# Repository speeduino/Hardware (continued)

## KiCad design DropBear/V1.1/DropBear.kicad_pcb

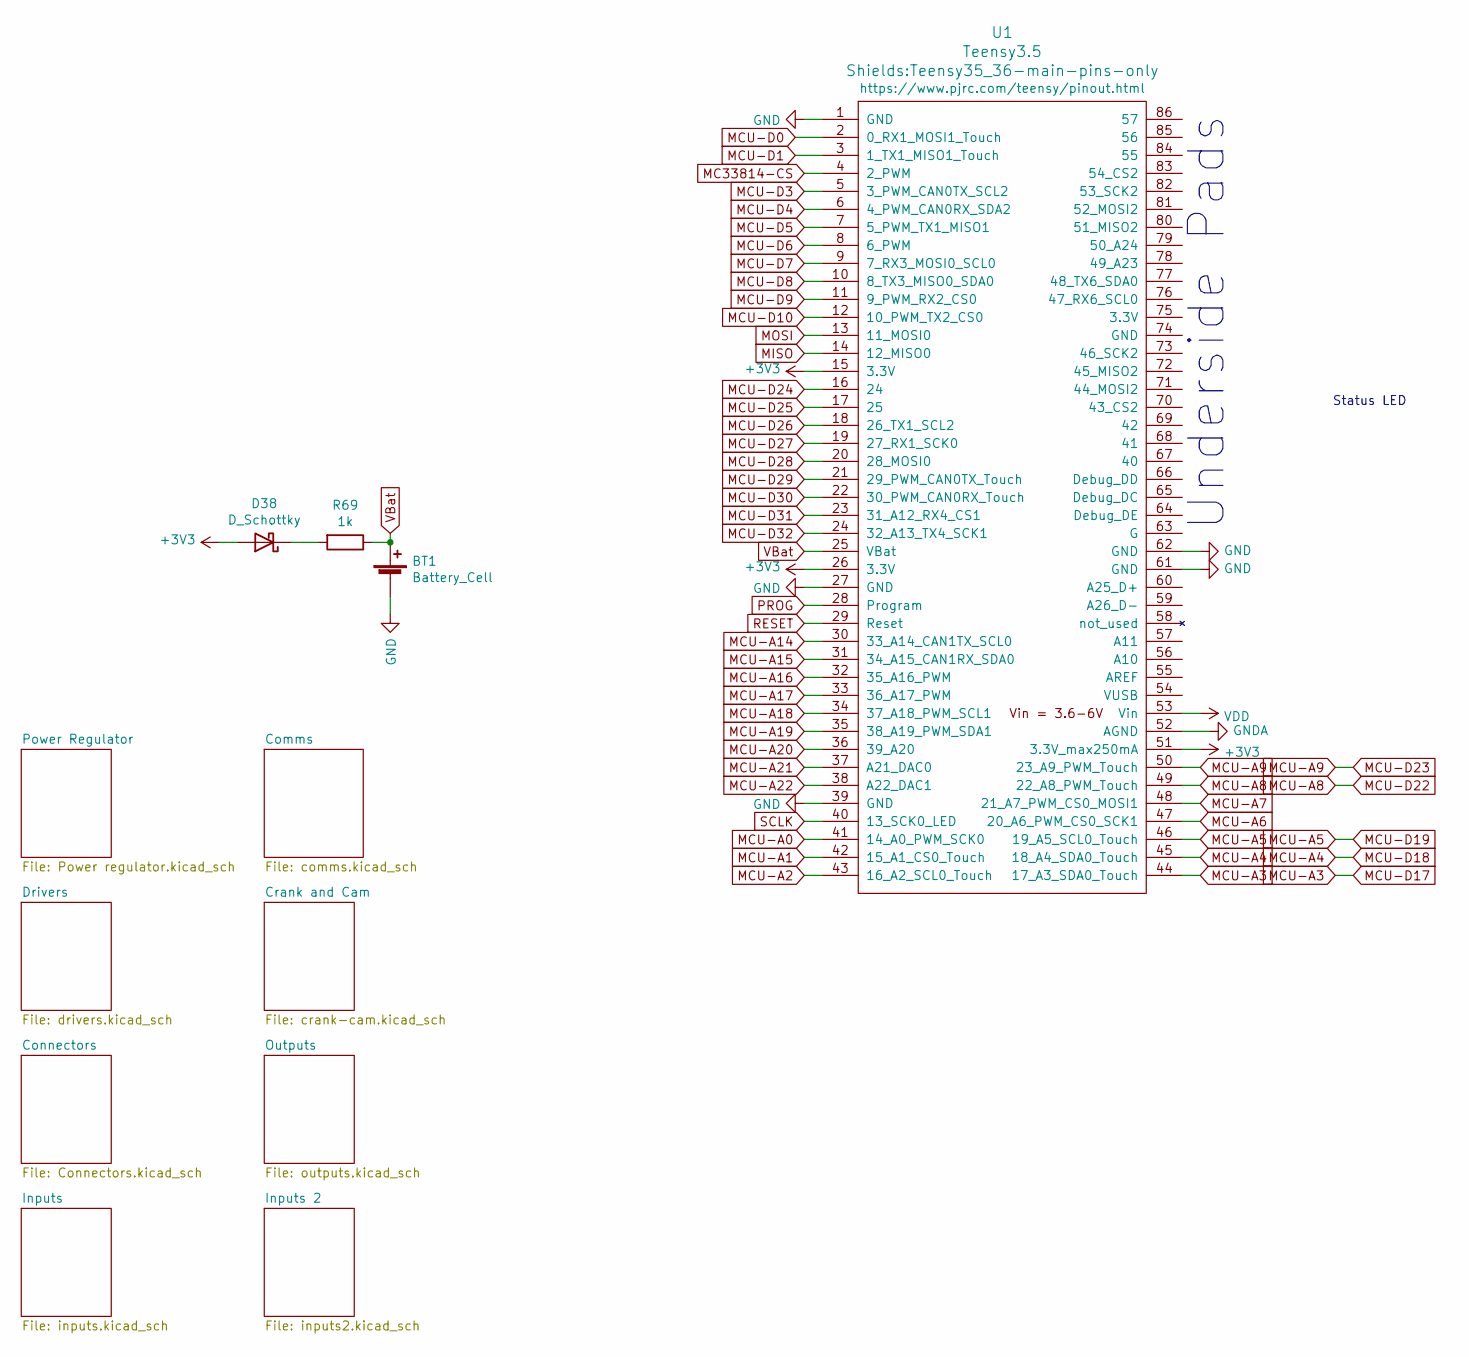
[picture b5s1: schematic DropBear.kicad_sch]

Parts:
BT1: Battery_Cell; 2999; Manufacturer_Part_Number 2999; Digikey Part Number 36-2999-ND
D38: D_Schottky; D_PowerDI-123; Manufacturer_Part_Number DFLS2100-7; Digikey Part Number DFLS2100-7DICT-ND
R69: 1k; R_0805_2012Metric; Manufacturer_Part_Number RC0805FR-071KL; Digikey Part Number 311-1.00KCRCT-ND
U1: Teensy3.5; Teensy35_36-main-pins-only

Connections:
+3V3: D38.2 (A), U1.15 (3.3V), U1.26 (3.3V), U1.51 (3.3V_max250mA); also elsewhere on the board
+5V: U1.53 (Vin); also elsewhere on the board
ADC-Clamp-3: U1.34 (37_A18_PWM_SCL1); also elsewhere on the board
ADC-Clamp-4: U1.33 (36_A17_PWM); also elsewhere on the board
ADC-Clamp-5: U1.32 (35_A16_PWM); also elsewhere on the board
ADC-Clamp-6: U1.31 (34_A15_CAN1RX_SDA0); also elsewhere on the board
ADC-Clamp-7: U1.30 (33_A14_CAN1TX_SCL0); also elsewhere on the board
ADC-Clamp-11: U1.35 (38_A19_PWM_SDA1); also elsewhere on the board
ADC-Clamp-12: U1.36 (39_A20); also elsewhere on the board
ADC-Clamp-13: U1.37 (A21_DAC0); also elsewhere on the board
ADC-Clamp-14: U1.38 (A22_DAC1); also elsewhere on the board
GND: BT1.2 (-), U1.1 (GND), U1.27 (GND), U1.39 (GND), U1.61 (GND), U1.62 (GND); also elsewhere on the board
GNDA: U1.52 (AGND); also elsewhere on the board
MC33810_1-CS: U1.12 (10_PWM_TX2_CS0); also elsewhere on the board
MC33810_2-CS: U1.11 (9_PWM_RX2_CS0); also elsewhere on the board
MC33814-CS: U1.4 (2_PWM); also elsewhere on the board
MCU-A0: U1.41 (14_A0_PWM_SCK0); also elsewhere on the board
MCU-A1: U1.42 (15_A1_CS0_Touch); also elsewhere on the board
MCU-A2: U1.43 (16_A2_SCL0_Touch)
MCU-A3: U1.44 (17_A3_SDA0_Touch)
MCU-A4: U1.45 (18_A4_SDA0_Touch); also elsewhere on the board
MCU-A5: U1.46 (19_A5_SCL0_Touch); also elsewhere on the board
MCU-A6: U1.47 (20_A6_PWM_CS0_SCK1)
MCU-A7: U1.48 (21_A7_PWM_CS0_MOSI1)
MCU-A8: U1.49 (22_A8_PWM_Touch); also elsewhere on the board
MCU-A9: U1.50 (23_A9_PWM_Touch); also elsewhere on the board
MCU-D0: U1.2 (0_RX1_MOSI1_Touch); also elsewhere on the board
MCU-D1: U1.3 (1_TX1_MISO1_Touch); also elsewhere on the board
MCU-D3: U1.5 (3_PWM_CAN0TX_SCL2); also elsewhere on the board
MCU-D4: U1.6 (4_PWM_CAN0RX_SDA2); also elsewhere on the board
MCU-D5: U1.7 (5_PWM_TX1_MISO1); also elsewhere on the board
MCU-D6: U1.8 (6_PWM); also elsewhere on the board
MCU-D7: U1.9 (7_RX3_MOSI0_SCL0); also elsewhere on the board
MCU-D8: U1.10 (8_TX3_MISO0_SDA0); also elsewhere on the board
MCU-D24: U1.16 (24); also elsewhere on the board
MCU-D25: U1.17 (25); also elsewhere on the board
MCU-D26: U1.18 (26_TX1_SCL2); also elsewhere on the board
MCU-D27: U1.19 (27_RX1_SCK0); also elsewhere on the board
MCU-D28: U1.20 (28_MOSI0); also elsewhere on the board
MCU-D29: U1.21 (29_PWM_CAN0TX_Touch); also elsewhere on the board
MCU-D30: U1.22 (30_PWM_CAN0RX_Touch); also elsewhere on the board
MCU-D31: U1.23 (31_A12_RX4_CS1); also elsewhere on the board
MCU-D32: U1.24 (32_A13_TX4_SCK1); also elsewhere on the board
MISO: U1.14 (12_MISO0); also elsewhere on the board
MOSI: U1.13 (11_MOSI0); also elsewhere on the board
unnamed: D38.1 (K), R69.2
PROG: U1.28 (Program)
RESET: U1.29 (Reset)
SCLK: U1.40 (13_SCK0_LED); also elsewhere on the board
VBat: BT1.1 (+), R69.1, U1.25 (VBat)

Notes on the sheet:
Underside Pads
Status LED

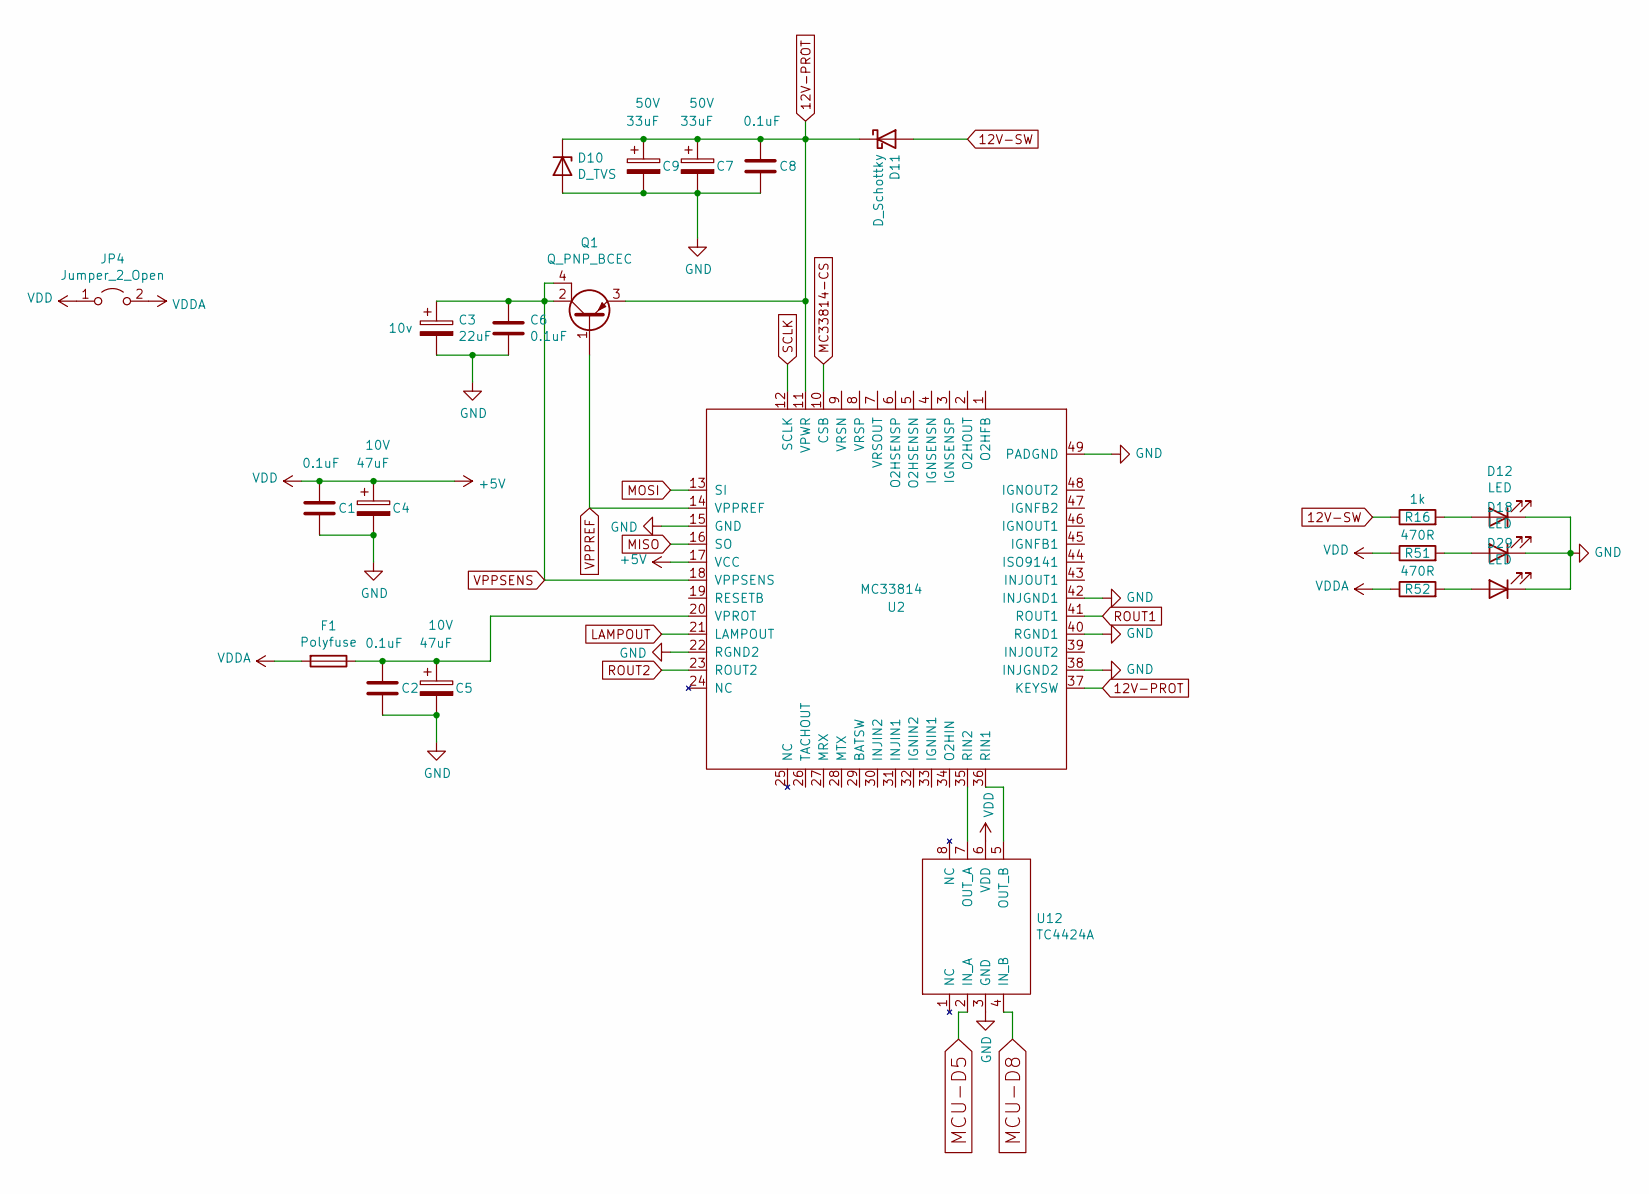
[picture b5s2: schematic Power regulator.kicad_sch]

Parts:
C1, C2, C6, C8: 0.1uF; C_0805_2012Metric; Manufacturer_Part_Number CC0805KRX7R9BB104; Digikey Part Number 311-1140-1-ND
C3: 22uF; CP_Elec_4x5.4; Voltage 10v; Manufacturer_Part_Number PCE3882CT-ND; Digikey Part Number EEE-1CA220WR
C4, C5: 47uF; CP_EIA-3528-21_Kemet-B; Voltage 10V; Manufacturer_Part_Number TAJB476K006RNJ; Digikey Part Number 478-1692-1-ND
C7, C9: 33uF; CP_Elec_6.3x7.7; Voltage 50V; Manufacturer_Part_Number EEE-1HA330XP; Digikey Part Number PCE3925CT-ND
D10: D_TVS; D_SMB; Manufacturer_Part_Number SMBJ40A-Q; Digikey Part Number SMBJ40A-QCT-ND
D11: D_Schottky; D_SMA_Handsoldering; Manufacturer_Part_Number B360A-13-F; Digikey Part Number B360A-FDICT-ND
D12, D18, D29: LED; LED_0805_2012Metric_Pad1.15x1.40mm_HandSolder; Manufacturer_Part_Number LG R971-KN-1; Digikey Part Number 475-1410-2-ND
F1: Polyfuse; Fuse_0603_1608Metric; Manufacturer_Part_Number 0ZCM0008FF2G; Digikey Part Number 507-1817-1-ND
JP4: Jumper_2_Open; SolderJumper-2_P1.3mm_Open_Pad1.0x1.5mm
Q1: Q_PNP_BCEC; SOT-223-3_TabPin2; Manufacturer_Part_Number FZT753TA; Digikey Part Number FZT753CT-ND
R16: 1k; R_0805_2012Metric; Manufacturer_Part_Number RC0805FR-071KL; Digikey Part Number 311-1.00KCRCT-ND
R51, R52: 470R; R_0805_2012Metric; Manufacturer_Part_Number ERJ-6ENF4700V; Digikey Part Number P470CCT-ND
U2: MC33814; LQFP-48-1EP_7x7mm_P0.5mm_EP3.6x3.6mm_ThermalVias; Manufacturer_Part_Number MC33814AE
U12: TC4424A; SOIC-8_3.9x4.9mm_P1.27mm; Manufacturer_Part_Number TC4424AVOA; Digikey Part Number TC4424AVOA-ND

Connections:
12V-PROT: C7.1, C8.1, C9.1, D10.1 (K), D11.1 (K), Q1.3 (E), U2.11 (VPWR), U2.37 (KEYSW)
12V-SW: D11.2 (A), R16.1; also elsewhere on the board
+5V: C1.1, C4.1, JP4.1 (A), R51.1, U2.17 (VCC), U12.6 (VDD); also elsewhere on the board
GND: C1.2, C2.2, C3.2, C4.2, C5.2, C6.2, C7.2, C8.2, C9.2, D10.2 (A), D12.1 (K), D18.1 (K), D29.1 (K), U2.15 (GND), U2.22 (RGND2), U2.38 (INJGND2), U2.40 (RGND1), U2.42 (INJGND1), U2.49 (PADGND), U12.3 (GND); also elsewhere on the board
LAMPOUT: U2.21 (LAMPOUT)
MC33814-CS: U2.10 (CSB); also elsewhere on the board
MCU-D5: U12.2 (IN_A); also elsewhere on the board
MCU-D8: U12.4 (IN_B); also elsewhere on the board
MISO: U2.16 (SO); also elsewhere on the board
MOSI: U2.13 (SI); also elsewhere on the board
unnamed: C2.1, C5.1, F1.1, U2.20 (VPROT)
unnamed: D12.2 (A), R16.2
unnamed: D18.2 (A), R51.2
unnamed: D29.2 (A), R52.2
unnamed: U2.36 (RIN1), U12.5 (OUT_B)
unnamed: U2.35 (RIN2), U12.7 (OUT_A)
ROUT2: U2.23 (ROUT2); also elsewhere on the board
SCLK: U2.12 (SCLK); also elsewhere on the board
VDDA: F1.2, JP4.2 (B), R52.1; also elsewhere on the board
VPPREF: Q1.1 (B), U2.14 (VPPREF)
VPPSENS: C3.1, C6.1, Q1.2 (C), Q1.4 (C), U2.18 (VPPSENS)

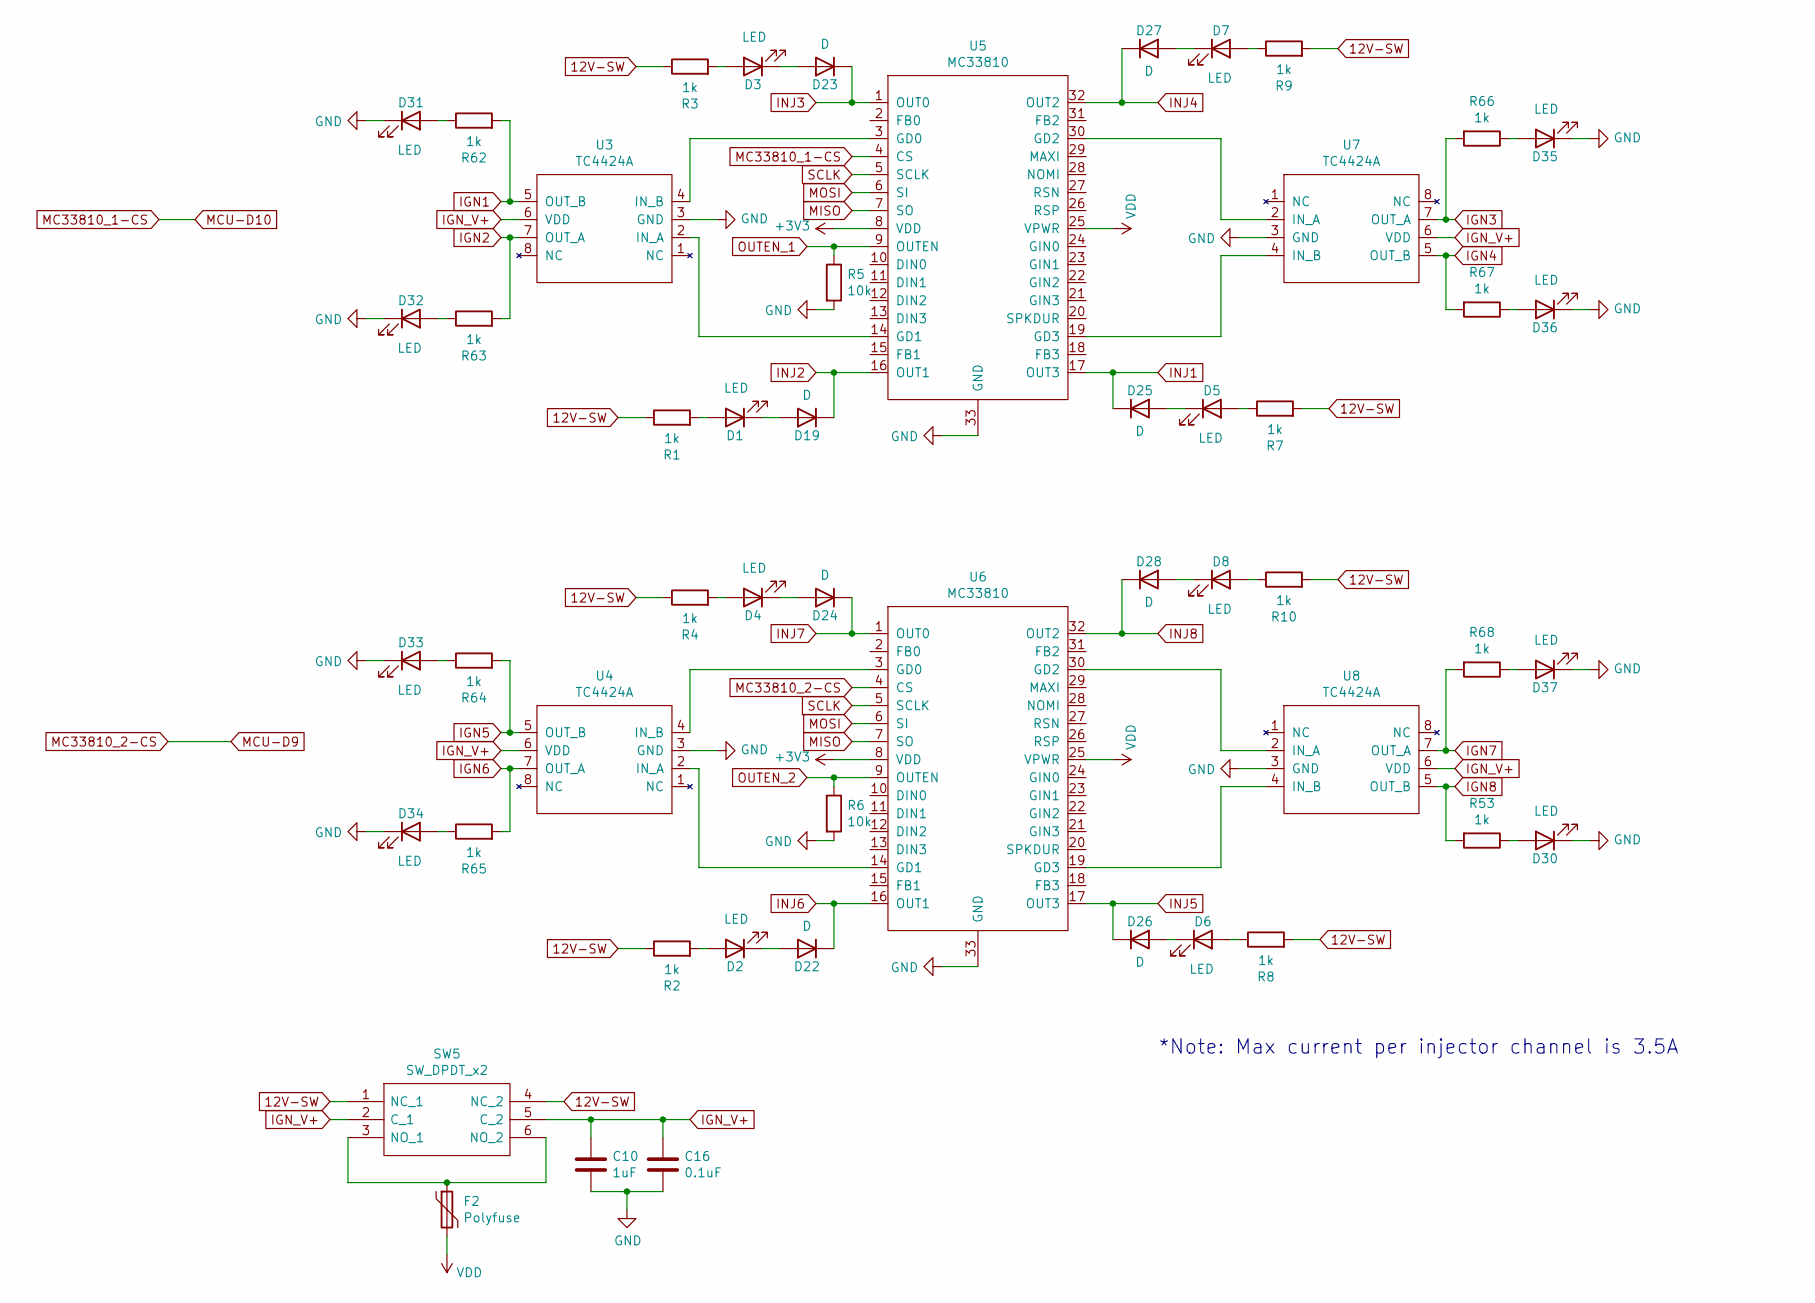
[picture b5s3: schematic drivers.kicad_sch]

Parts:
C10: 1uF; C_0805_2012Metric; Manufacturer_Part_Number CC0805KKX7R7BB105; Digikey Part Number 311-1365-1-ND
C16: 0.1uF; C_0805_2012Metric; Manufacturer_Part_Number CC0805KRX7R9BB104; Digikey Part Number 311-1140-1-ND
D1, D2, D3, D4, D5, D6, D7, D8: LED; LED_0805_2012Metric; Manufacturer_Part_Number LH R974-LP-1; Digikey Part Number 475-1415-1-ND
D19, D22, D23, D24, D25, D26, D27, D28: D; D_SOD-323; Manufacturer_Part_Number 1N4448WX-TP; Digikey Part Number 1N4448WXTPMSCT-ND
D30, D31, D32, D33, D34, D35, D36, D37: LED; LED_0805_2012Metric; Manufacturer_Part_Number SML-H12D8TT86C; Digikey Part Number SML-H12D8TT86CCT-ND
F2: Polyfuse; Fuse_1812_4532Metric; Manufacturer_Part_Number 0ZCC0050FF2C; Digikey Part Number 507-1361-1-ND
R1, R2, R3, R4, R7, R8, R9, R10, R53, R62, R63, R64, R65, R66, R67, R68: 1k; R_0805_2012Metric; Manufacturer_Part_Number RC0805FR-071KL; Digikey Part Number 311-1.00KCRCT-ND
R5, R6: 10k; R_0805_2012Metric; Manufacturer_Part_Number RC0805JR-0710KL; Digikey Part Number 311-10KARCT-ND
SW5: SW_DPDT_x2; AYZ0202AGRLC; Manufacturer_Part_Number AYZ0202AGRLC; Digikey Part Number 401-2013-1-ND
U3, U4, U7, U8: TC4424A; SOIC-8_3.9x4.9mm_P1.27mm; Manufacturer_Part_Number TC4424AVOA; Digikey Part Number TC4424AVOA-ND
U5, U6: MC33810; SOIC32-P0.65-33N; Manufacturer_Part_Number MCZ33810EK

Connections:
12V-SW: R1.1, R2.1, R3.1, R4.1, R7.2, R8.2, R9.2, R10.2, SW5.1 (NC_1), SW5.4 (NC_2); also elsewhere on the board
+3V3: U5.8 (VDD), U6.8 (VDD); also elsewhere on the board
+5V: F2.2, U5.25 (VPWR), U6.25 (VPWR); also elsewhere on the board
GND: C10.2, C16.2, D30.1 (K), D31.1 (K), D32.1 (K), D33.1 (K), D34.1 (K), D35.1 (K), D36.1 (K), D37.1 (K), R5.2, R6.2, U3.3 (GND), U4.3 (GND), U5.33 (GND), U6.33 (GND), U7.3 (GND), U8.3 (GND); also elsewhere on the board
IGN1: R62.2, U3.5 (OUT_B); also elsewhere on the board
IGN2: R63.2, U3.7 (OUT_A); also elsewhere on the board
IGN3: R66.2, U7.7 (OUT_A); also elsewhere on the board
IGN4: R67.2, U7.5 (OUT_B); also elsewhere on the board
IGN5: R64.2, U4.5 (OUT_B); also elsewhere on the board
IGN6: R65.2, U4.7 (OUT_A); also elsewhere on the board
IGN7: R68.2, U8.7 (OUT_A); also elsewhere on the board
IGN8: R53.2, U8.5 (OUT_B); also elsewhere on the board
IGN_V+: C10.1, C16.1, SW5.2 (C_1), SW5.5 (C_2), U3.6 (VDD), U4.6 (VDD), U7.6 (VDD), U8.6 (VDD)
INJ1: D25.1 (K), U5.17 (OUT3); also elsewhere on the board
INJ2: D19.1 (K), U5.16 (OUT1); also elsewhere on the board
INJ3: D23.1 (K), U5.1 (OUT0); also elsewhere on the board
INJ4: D27.1 (K), U5.32 (OUT2); also elsewhere on the board
INJ5: D26.1 (K), U6.17 (OUT3); also elsewhere on the board
INJ6: D22.1 (K), U6.16 (OUT1); also elsewhere on the board
INJ7: D24.1 (K), U6.1 (OUT0); also elsewhere on the board
INJ8: D28.1 (K), U6.32 (OUT2); also elsewhere on the board
MC33810_1-CS: U5.4 (CS); also elsewhere on the board
MC33810_2-CS: U6.4 (CS); also elsewhere on the board
MISO: U5.7 (SO), U6.7 (SO); also elsewhere on the board
MOSI: U5.6 (SI), U6.6 (SI); also elsewhere on the board
unnamed: D1.1 (K), D19.2 (A)
unnamed: D1.2 (A), R1.2
unnamed: D2.1 (K), D22.2 (A)
unnamed: D2.2 (A), R2.2
unnamed: D3.2 (A), R3.2
unnamed: D4.2 (A), R4.2
unnamed: D5.2 (A), R7.1
unnamed: D6.2 (A), R8.1
unnamed: D7.2 (A), R9.1
unnamed: D8.2 (A), R10.1
unnamed: D3.1 (K), D23.2 (A)
unnamed: D4.1 (K), D24.2 (A)
unnamed: D5.1 (K), D25.2 (A)
unnamed: D6.1 (K), D26.2 (A)
unnamed: D7.1 (K), D27.2 (A)
unnamed: D8.1 (K), D28.2 (A)
unnamed: D30.2 (A), R53.1
unnamed: D31.2 (A), R62.1
unnamed: D32.2 (A), R63.1
unnamed: D33.2 (A), R64.1
unnamed: D34.2 (A), R65.1
unnamed: D35.2 (A), R66.1
unnamed: D36.2 (A), R67.1
unnamed: D37.2 (A), R68.1
unnamed: F2.1, SW5.3 (NO_1), SW5.6 (NO_2)
unnamed: U3.2 (IN_A), U5.14 (GD1)
unnamed: U3.4 (IN_B), U5.3 (GD0)
unnamed: U4.2 (IN_A), U6.14 (GD1)
unnamed: U4.4 (IN_B), U6.3 (GD0)
unnamed: U5.19 (GD3), U7.4 (IN_B)
unnamed: U5.30 (GD2), U7.2 (IN_A)
unnamed: U6.19 (GD3), U8.4 (IN_B)
unnamed: U6.30 (GD2), U8.2 (IN_A)
OUTEN_1: R5.1, U5.9 (OUTEN)
OUTEN_2: R6.1, U6.9 (OUTEN)
SCLK: U5.5 (SCLK), U6.5 (SCLK); also elsewhere on the board

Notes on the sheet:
*Note: Max current per injector channel is 3.5A

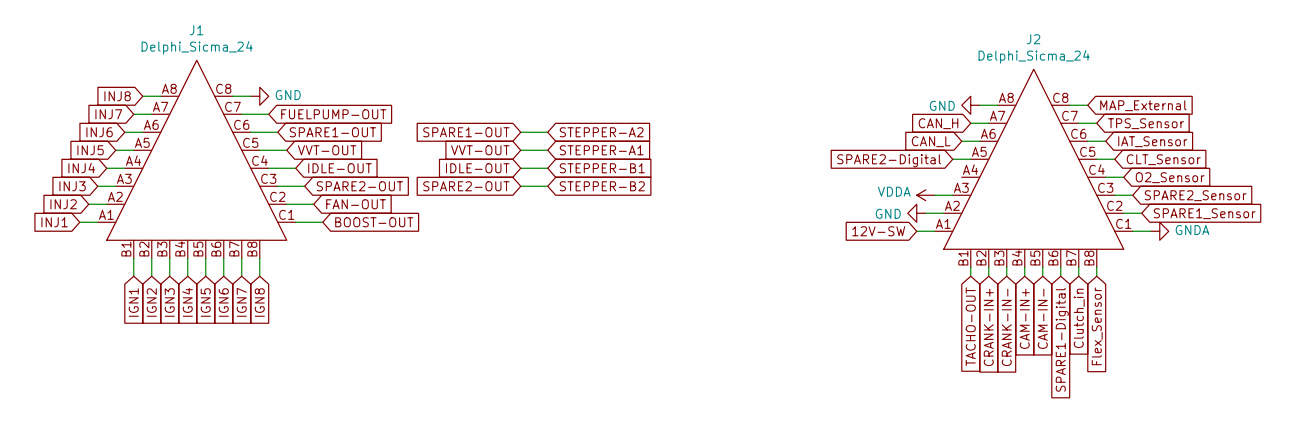
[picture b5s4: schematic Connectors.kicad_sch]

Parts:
J1: Delphi_Sicma_24; Delphi_Sicma_24_Grey
J2: Delphi_Sicma_24; Delphi_Sicma_24_Black

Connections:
12V-SW: J2.A1; also elsewhere on the board
ADC-Clamp-5: J2.B8; also elsewhere on the board
ADC-Clamp-6: J2.B7; also elsewhere on the board
BOOST-OUT: J1.C1; also elsewhere on the board
CAM-IN+: J2.B4; also elsewhere on the board
CAM-IN-: J2.B5; also elsewhere on the board
CAN_H: J2.A7; also elsewhere on the board
CAN_L: J2.A6; also elsewhere on the board
CLT_Sensor: J2.C5; also elsewhere on the board
CRANK-IN+: J2.B2; also elsewhere on the board
CRANK-IN-: J2.B3; also elsewhere on the board
FAN-OUT: J1.C2; also elsewhere on the board
GND: J1.C8, J2.A2, J2.A8; also elsewhere on the board
GNDA: J2.C1; also elsewhere on the board
IAT_Sensor: J2.C6; also elsewhere on the board
IDLE-OUT: J1.C4; also elsewhere on the board
IGN1: J1.B1; also elsewhere on the board
IGN2: J1.B2; also elsewhere on the board
IGN3: J1.B3; also elsewhere on the board
IGN4: J1.B4; also elsewhere on the board
IGN5: J1.B5; also elsewhere on the board
IGN6: J1.B6; also elsewhere on the board
IGN7: J1.B7; also elsewhere on the board
IGN8: J1.B8; also elsewhere on the board
INJ1: J1.A1; also elsewhere on the board
INJ2: J1.A2; also elsewhere on the board
INJ3: J1.A3; also elsewhere on the board
INJ4: J1.A4; also elsewhere on the board
INJ5: J1.A5; also elsewhere on the board
INJ6: J1.A6; also elsewhere on the board
INJ7: J1.A7; also elsewhere on the board
INJ8: J1.A8; also elsewhere on the board
MAP_External: J2.C8; also elsewhere on the board
O2_Sensor: J2.C4; also elsewhere on the board
ROUT2: J2.B1; also elsewhere on the board
SPARE1-Digital: J2.B6; also elsewhere on the board
SPARE1-OUT: J1.C6; also elsewhere on the board
SPARE1_Sensor: J2.C2; also elsewhere on the board
SPARE2-Digital: J2.A5; also elsewhere on the board
SPARE2-OUT: J1.C3; also elsewhere on the board
SPARE2_Sensor: J2.C3; also elsewhere on the board
STEPPER-A1: J1.C5; also elsewhere on the board
TPS_Sensor: J2.C7; also elsewhere on the board
VDDA: J2.A3; also elsewhere on the board

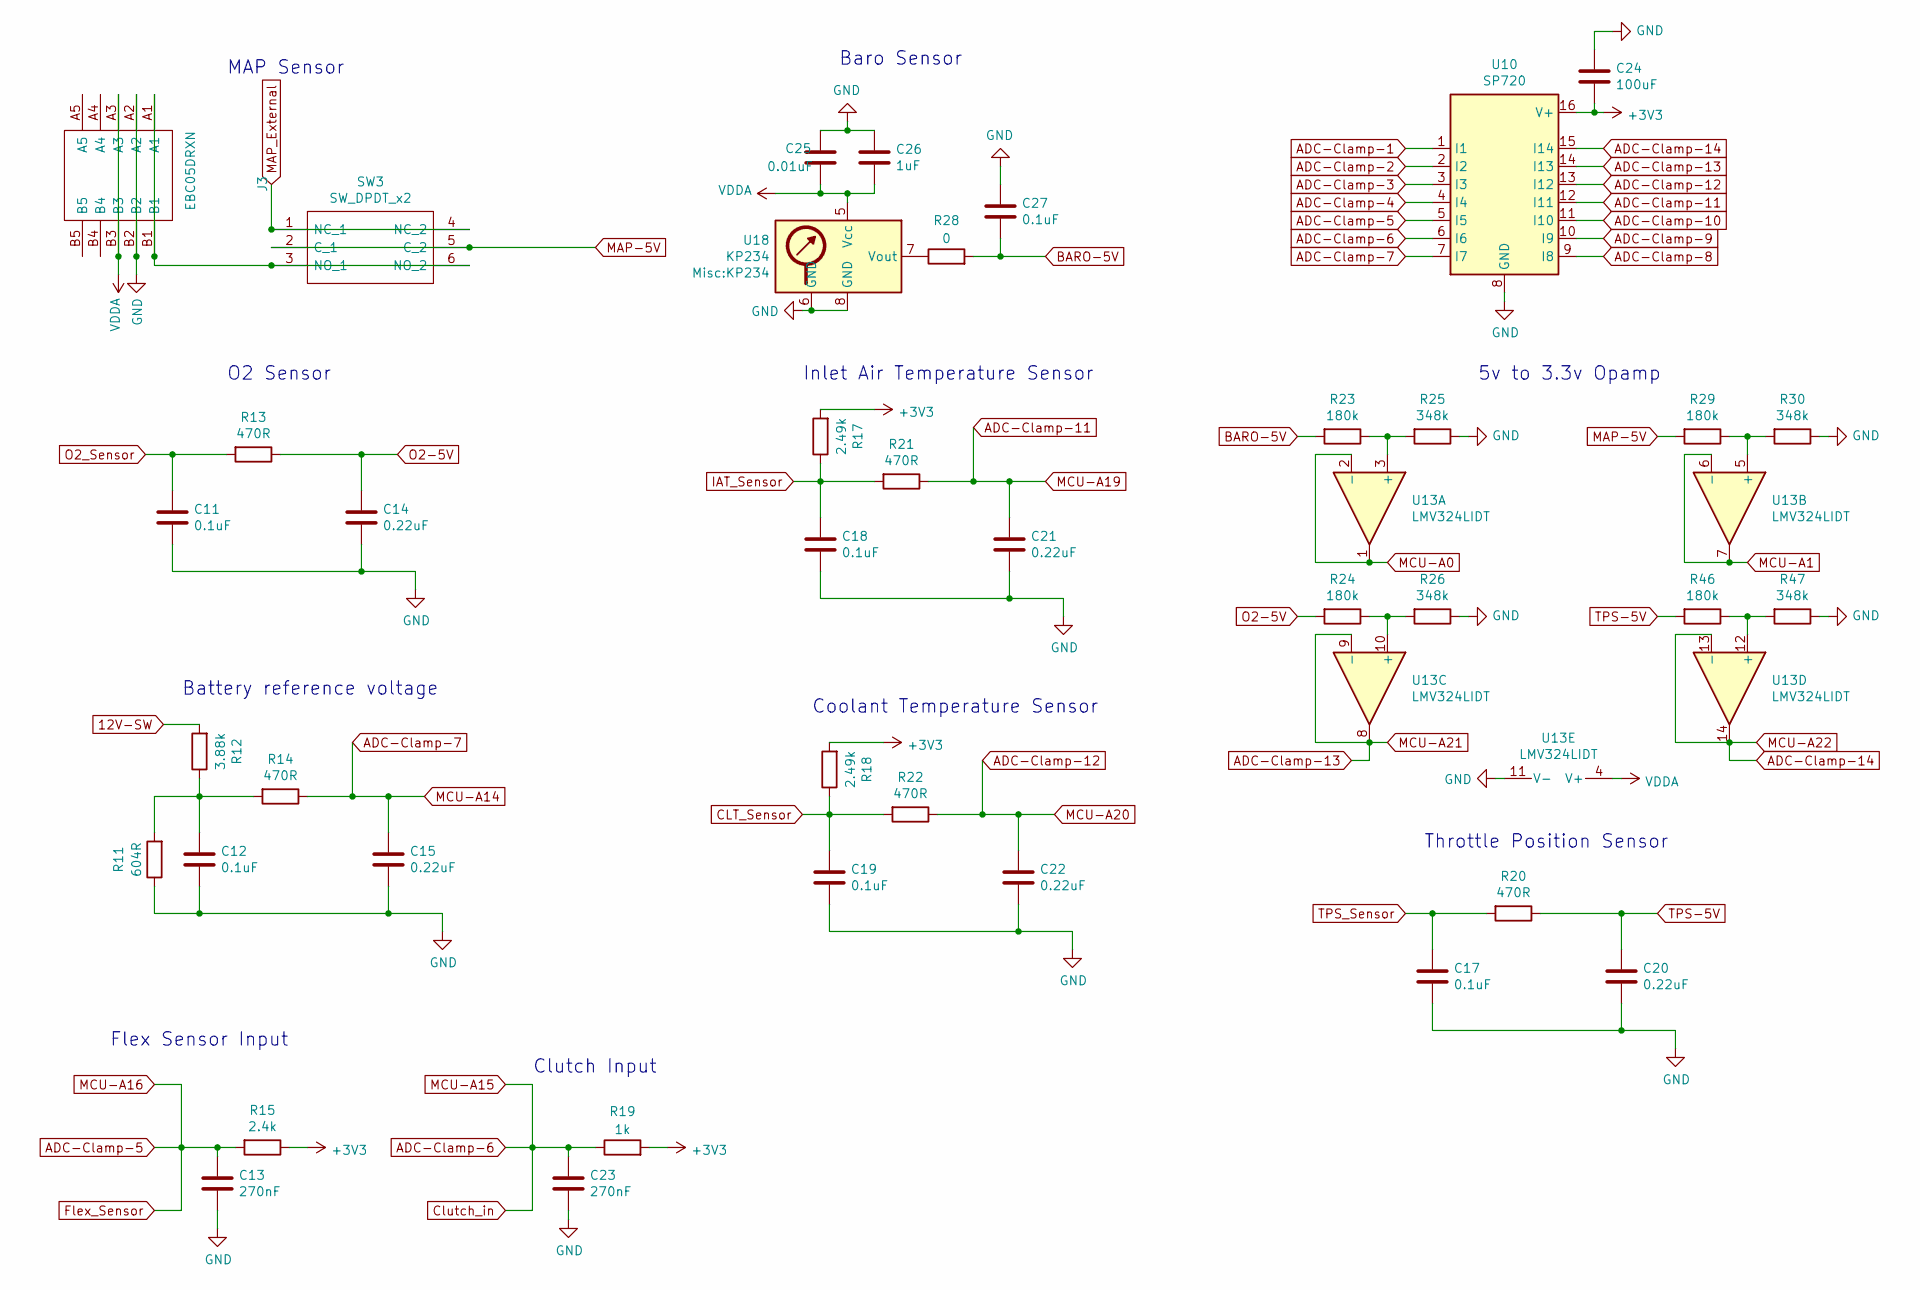
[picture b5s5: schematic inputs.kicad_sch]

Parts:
C11, C12, C17, C18, C19, C27: 0.1uF; C_0805_2012Metric; Manufacturer_Part_Number CC0805KRX7R9BB104; Digikey Part Number 311-1140-1-ND
C13, C23: 270nF; C_0805_2012Metric; Manufacturer_Part_Number CC0805JRX7R7BB274; Digikey Part Number 311-4268-1-ND
C14, C15, C20, C21, C22: 0.22uF; C_0805_2012Metric; Manufacturer_Part_Number CL21B224KOCNNNC; Digikey Part Number 1276-1284-1-ND
C24: 100uF; C_1206_3216Metric; Manufacturer_Part_Number CL31A107MQHNNNE; Digikey Part Number 1276-1782-1-ND
C25: 0.01uF; C_0805_2012Metric; Manufacturer_Part_Number CC0805KRX7R9BB103; Digikey Part Number 311-1136-1-ND
C26: 1uF; C_0805_2012Metric; Manufacturer_Part_Number CC0805KKX7R7BB105; Digikey Part Number 311-1365-1-ND
J3: EBC05DRXN; Manufacturer_Part_Number EBC05DRXN; Digikey Part Number S9641-ND
R11: 604R; R_0805_2012Metric; Tolerance 1%; Manufacturer_Part_Number RC0805FR-07604RL; Digikey Part Number 311-604CRCT-ND
R12: 3.88k; R_0603_1608Metric_Pad1.05x0.95mm_HandSolder; Tolerance 1%; Manufacturer_Part_Number RT0603BRD073K88L; Digikey Part Number YAG4550CT-ND
R13, R14, R20, R21, R22: 470R; R_0805_2012Metric; Manufacturer_Part_Number ERJ-6ENF4700V; Digikey Part Number P470CCT-ND
R15: 2.4k; R_0805_2012Metric; Manufacturer_Part_Number RC0805FR-072K4L; Digikey Part Number 311-2.40KCRCT-ND
R17, R18: 2.49k; R_0805_2012Metric; Tolerance 0.1%; Manufacturer_Part_Number RT0805BRD072K49L; Digikey Part Number YAG1854CT-ND
R19: 1k; R_0805_2012Metric; Manufacturer_Part_Number RC0805FR-071KL; Digikey Part Number 311-1.00KCRCT-ND
R23, R24, R29, R46: 180k; R_0805_2012Metric; Manufacturer_Part_Number RC0805FR-07180KL; Digikey Part Number 311-180KCRCT-ND
R25, R26, R30, R47: 348k; R_0805_2012Metric; Manufacturer_Part_Number ERJ-6ENF3483V; Digikey Part Number P348KCDKR-ND
R28: 0; R_0805_2012Metric; Manufacturer_Part_Number ERJ-6GEY0R00V; Digikey Part Number P0.0ACT-ND
SW3: SW_DPDT_x2; AYZ0202AGRLC; Manufacturer_Part_Number AYZ0202AGRLC; Digikey Part Number 401-2013-1-ND
U10: SP720; SOIC-16_3.9x9.9mm_P1.27mm; Manufacturer_Part_Number SP720ABTG; Digikey Part Number F3162CT-ND
U13: LMV324LIDT; SOIC-14_3.9x8.7mm_P1.27mm; Manufacturer_Part_Number LMV324LIDT; Digikey Part Number 497-13052-1-ND
U18: KP234; Manufacturer_Part_Number KP234XTMA1; Digikey Part Number 448-KP234XTMA1CT-ND

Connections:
12V-SW: R12.2; also elsewhere on the board
+3V3: C24.2, R15.1, R17.2, R18.2, R19.2, U10.16 (V+); also elsewhere on the board
ADC-Clamp-1: U10.1 (I1)
ADC-Clamp-2: U10.2 (I2)
ADC-Clamp-3: U10.3 (I3); also elsewhere on the board
ADC-Clamp-4: U10.4 (I4); also elsewhere on the board
ADC-Clamp-5: C13.1, R15.2, U10.5 (I5); also elsewhere on the board
ADC-Clamp-6: C23.1, R19.1, U10.6 (I6); also elsewhere on the board
ADC-Clamp-7: C15.1, R14.1, U10.7 (I7); also elsewhere on the board
ADC-Clamp-8: U10.9 (I8)
ADC-Clamp-9: U10.10 (I9)
ADC-Clamp-10: U10.11 (I10)
ADC-Clamp-11: C21.1, R21.1, U10.12 (I11); also elsewhere on the board
ADC-Clamp-12: C22.1, R22.1, U10.13 (I12); also elsewhere on the board
ADC-Clamp-13: U10.14 (I13), U13.8, U13.9 (-); also elsewhere on the board
ADC-Clamp-14: U10.15 (I14), U13.13 (-), U13.14; also elsewhere on the board
BARO-5V: C27.2, R23.2, R28.2
CLT_Sensor: C19.1, R18.1, R22.2; also elsewhere on the board
GND: C11.2, C12.2, C13.2, C14.2, C15.2, C17.2, C18.2, C19.2, C20.2, C21.2, C22.2, C23.2, C24.1, C25.1, C26.1, C27.1, J3.A2, J3.B2, R11.1, R25.1, R26.1, R30.1, R47.1, U10.8 (GND), U13.11 (V-), U18.6 (GND), U18.8 (GND); also elsewhere on the board
IAT_Sensor: C18.1, R17.1, R21.2; also elsewhere on the board
MAP-5V: R29.2, SW3.2 (C_1), SW3.5 (C_2)
MAP_External: SW3.1 (NC_1), SW3.4 (NC_2); also elsewhere on the board
MCU-A0: U13.1, U13.2 (-); also elsewhere on the board
MCU-A1: U13.6 (-), U13.7; also elsewhere on the board
unnamed: C12.1, R11.2, R12.1, R14.2
unnamed: J3.A1, J3.B1, SW3.3 (NO_1), SW3.6 (NO_2)
unnamed: R23.1, R25.2, U13.3 (+)
unnamed: R24.1, R26.2, U13.10 (+)
unnamed: R28.1, U18.7 (Vout)
unnamed: R29.1, R30.2, U13.5 (+)
unnamed: R46.1, R47.2, U13.12 (+)
O2-5V: C14.1, R13.1, R24.2
O2_Sensor: C11.1, R13.2; also elsewhere on the board
TPS-5V: C20.1, R20.1, R46.2
TPS_Sensor: C17.1, R20.2; also elsewhere on the board
VDDA: C25.2, C26.2, J3.A3, J3.B3, U13.4 (V+), U18.5 (Vcc); also elsewhere on the board

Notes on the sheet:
5v to 3.3v Opamp
Inlet Air Temperature Sensor
Battery reference voltage
Flex Sensor Input
Coolant Temperature Sensor
Throttle Position Sensor
Baro Sensor
Clutch Input
MAP Sensor
O2 Sensor
